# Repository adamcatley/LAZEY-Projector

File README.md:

LAZEY-Projector
===============

Collection of LAZEY Projector related files, split into firmware, software and hardware.

See http://lazeyprojector.blogspot.co.uk for more information.

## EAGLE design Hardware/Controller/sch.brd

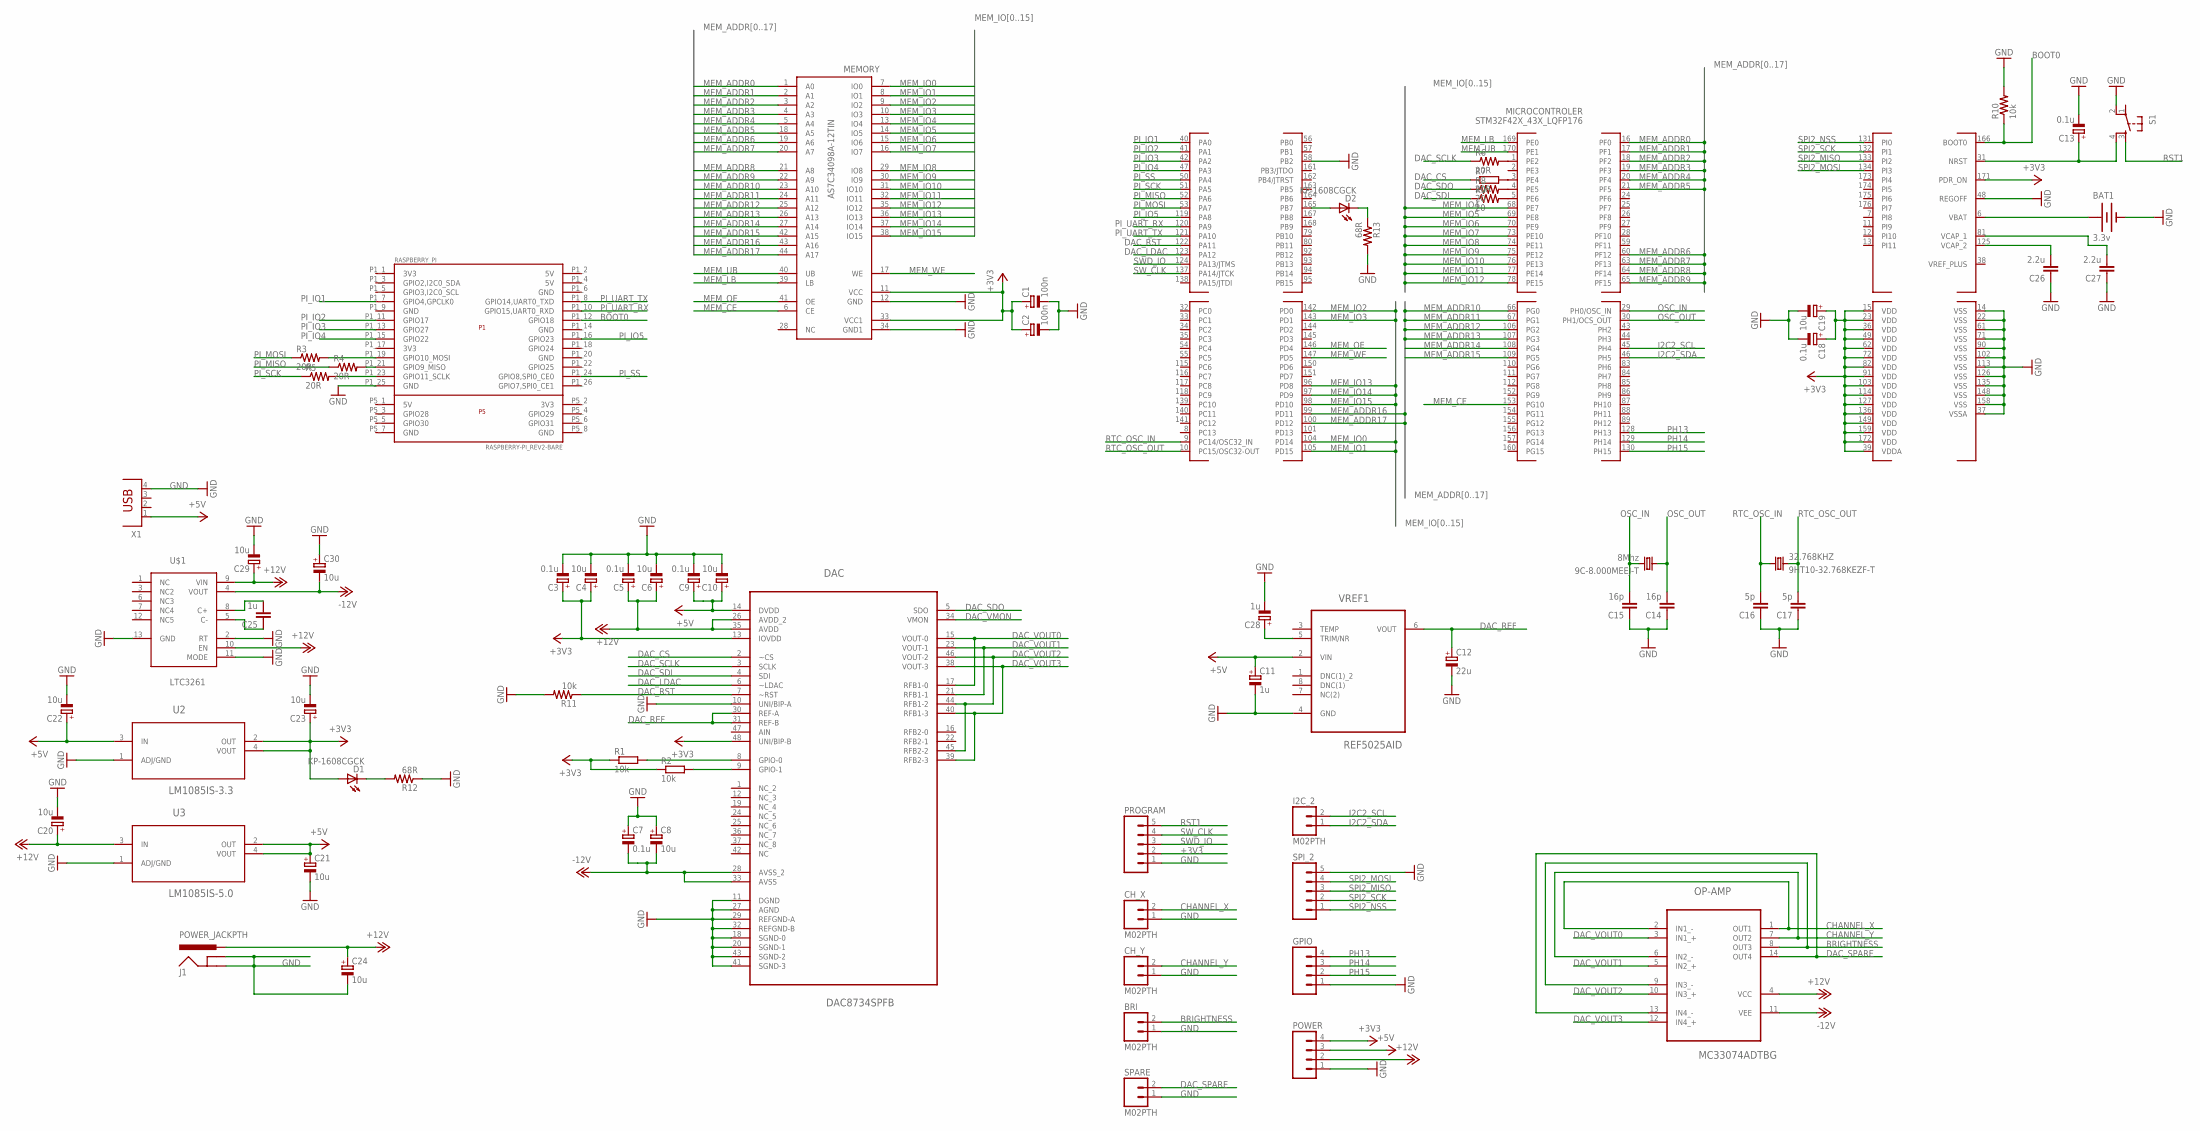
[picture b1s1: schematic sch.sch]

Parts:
9C-8.000MEEJ-T: 8Mhz; CSM-7X-DU
32.768KHZ: 9HT10-32.768KEZF-T
BAT1: 3.3v; BATTCON_12MM
BRI: M02PTH; 1X02
C1, C2: 100n; SMC_A
C3, C5, C7, C9, C13, C18: 0.1u; SMC_A
C4, C6, C8, C10, C19, C20, C21, C22, C23, C24, C29, C30: 10u; SMC_A
C11, C28: 1u; SMC_A
C12: 22u; SMC_A
C14, C15: 16p; C0603
C16, C17: 5p; C0603
C25: 1u; C0603
C26, C27: 2.2u; C0603
CH_X: M02PTH; 1X02
CH_Y: M02PTH; 1X02
D1, D2: KP-1608CGCK; LED-0603
DAC: DAC8734SPFB; QFP50P900X900X120-48N
GPIO: M04PTH; 1X04
I2C_2: M02PTH; 1X02
J1: POWER_JACKPTH; POWER_JACK_PTH
MEMORY: AS7C34098A-12TIN; TSOPII-44
MICROCONTROLER: STM32F42X_43X_LQFP176; LQFP176_PACKAGE
OP-AMP: MC33074ADTBG; SOP65P640X120-14N
POWER: M04PTH; 1X04
PROGRAM: M05PTH; 1X05
R1, R2: 10k; R0805
R3, R4, R5, R6: 20R; 0603-RES
R7: 20R; R0603
R8, R9: 20; 0603-RES
R10, R11: 10k; 0603-RES
R12, R13: 68R; 0603-RES
RASPBERRY_PI: RASPBERRY-PI_REV2-BARE
S1: TAC_SWITCHSMD; TACTILE_SWITCH_SMD
SPARE: M02PTH; 1X02
SPI_2: M05PTH; 1X05
U2: LM1085IS-3.3; TO254P1435X457-3N
U3: LM1085IS-5.0; TO254P1435X457-3N
U$1: LTC3261; MSOP12
VREF1: REF5025AID; SOIC127P600X175-8N
X1: PN87520

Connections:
+3V3: C1.+, C2.+, C3.+, C4.+, C18.+, C19.+, C23.+, D1.A, DAC.13 (IOVDD), DAC.48 (UNI/BIP-B), MEMORY.11 (VCC), MEMORY.33 (VCC1), MICROCONTROLER.15 (VDD), MICROCONTROLER.23 (VDD), MICROCONTROLER.36 (VDD), MICROCONTROLER.39 (VDDA), MICROCONTROLER.49 (VDD), MICROCONTROLER.62 (VDD), MICROCONTROLER.72 (VDD), MICROCONTROLER.82 (VDD), MICROCONTROLER.91 (VDD), MICROCONTROLER.103 (VDD), MICROCONTROLER.114 (VDD), MICROCONTROLER.127 (VDD), MICROCONTROLER.136 (VDD), MICROCONTROLER.149 (VDD), MICROCONTROLER.159 (VDD), MICROCONTROLER.171 (PDR_ON), MICROCONTROLER.172 (VDD), POWER.4, PROGRAM.2, R1.1, R2.1, U2.2 (OUT), U2.4 (VOUT)
+5V: C9.+, C10.+, C11.+, C21.+, C22.+, DAC.14 (DVDD), POWER.3, U2.3 (IN), U3.2 (OUT), U3.4 (VOUT), VREF1.2 (VIN), X1.1
+12V: C5.+, C6.+, C20.+, C24.+, C29.+, DAC.26 (AVDD_2), DAC.35 (AVDD), J1.PWR, OP-AMP.4 (VCC), POWER.2, U3.3 (IN), U$1.9 (VIN), U$1.10 (EN)
-12V: C7.-, C8.-, C30.-, DAC.28 (AVSS_2), DAC.33 (AVSS), OP-AMP.11 (VEE), U$1.4 (VOUT)
BOOT0: MICROCONTROLER.166 (BOOT0), R10.1, RASPBERRY_PI.P1_12 (GPIO18)
BRIGHTNESS: BRI.2, OP-AMP.8 (OUT3), OP-AMP.9 (IN3_-)
CHANNEL_X: CH_X.2, OP-AMP.1 (OUT1), OP-AMP.2 (IN1_-)
CHANNEL_Y: CH_Y.2, OP-AMP.6 (IN2_-), OP-AMP.7 (OUT2)
DAC_CS: DAC.2 (~CS), R7.1
DAC_LDAC: DAC.6 (~LDAC), MICROCONTROLER.123 (PA12)
DAC_REF: C12.+, DAC.30 (REF-A), DAC.31 (REF-B), VREF1.6 (VOUT)
DAC_RST: DAC.7 (~RST), MICROCONTROLER.122 (PA11), R11.1
DAC_SCLK: DAC.3 (SCLK), R6.1
DAC_SDI: DAC.4 (SDI), R9.1
DAC_SDO: DAC.5 (SDO), R8.1
DAC_SPARE: OP-AMP.13 (IN4_-), OP-AMP.14 (OUT4), SPARE.2
DAC_VMON: DAC.34 (VMON)
DAC_VOUT0: DAC.15 (VOUT-0), DAC.17 (RFB1-0), OP-AMP.3 (IN1_+)
DAC_VOUT1: DAC.21 (RFB1-1), DAC.23 (VOUT-1), OP-AMP.5 (IN2_+)
DAC_VOUT2: DAC.44 (RFB1-2), DAC.45 (RFB2-2), DAC.46 (VOUT-2), OP-AMP.10 (IN3_+)
DAC_VOUT3: DAC.38 (VOUT-3), DAC.39 (RFB2-3), DAC.40 (RFB1-3), OP-AMP.12 (IN4_+)
GND: BAT1.GND (-), BRI.1, C1.-, C2.-, C3.-, C4.-, C5.-, C6.-, C7.+, C8.+, C9.-, C10.-, C11.-, C12.-, C13.-, C14.1, C15.1, C16.1, C17.1, C18.-, C19.-, C20.-, C21.-, C22.-, C23.-, C24.-, C26.1, C27.1, C28.-, C29.-, C30.+, CH_X.1, CH_Y.1, DAC.10 (UNI/BIP-A), DAC.11 (DGND), DAC.18 (SGND-0), DAC.20 (SGND-1), DAC.27 (AGND), DAC.29 (REFGND-A), DAC.32 (REFGND-B), DAC.41 (SGND-3), DAC.43 (SGND-2), GPIO.1, J1.GND, J1.GNDBREAK, MEMORY.12 (GND), MEMORY.34 (GND1), MICROCONTROLER.14 (VSS), MICROCONTROLER.22 (VSS), MICROCONTROLER.37 (VSSA), MICROCONTROLER.48 (REGOFF), MICROCONTROLER.58 (PB2), MICROCONTROLER.61 (VSS), MICROCONTROLER.71 (VSS), MICROCONTROLER.90 (VSS), MICROCONTROLER.102 (VSS), MICROCONTROLER.113 (VSS), MICROCONTROLER.126 (VSS), MICROCONTROLER.135 (VSS), MICROCONTROLER.148 (VSS), MICROCONTROLER.158 (VSS), POWER.1, PROGRAM.1, R10.2, R11.2, R12.1, R13.2, RASPBERRY_PI.P1_25 (GND), S1.2, SPARE.1, SPI_2.5, U2.1 (ADJ/GND), U3.1 (ADJ/GND), U$1.2 (RT), U$1.11 (MODE), U$1.13 (GND), VREF1.4 (GND), X1.4
I2C2_SCL: I2C_2.2, MICROCONTROLER.45 (PH4)
I2C2_SDA: I2C_2.1, MICROCONTROLER.46 (PH5)
MEM_ADDR0: MEMORY.1 (A0), MICROCONTROLER.16 (PF0)
MEM_ADDR1: MEMORY.2 (A1), MICROCONTROLER.17 (PF1)
MEM_ADDR2: MEMORY.3 (A2), MICROCONTROLER.18 (PF2)
MEM_ADDR3: MEMORY.4 (A3), MICROCONTROLER.19 (PF3)
MEM_ADDR4: MEMORY.5 (A4), MICROCONTROLER.20 (PF4)
MEM_ADDR5: MEMORY.18 (A5), MICROCONTROLER.21 (PF5)
MEM_ADDR6: MEMORY.19 (A6), MICROCONTROLER.60 (PF12)
MEM_ADDR7: MEMORY.20 (A7), MICROCONTROLER.63 (PF13)
MEM_ADDR8: MEMORY.21 (A8), MICROCONTROLER.64 (PF14)
MEM_ADDR9: MEMORY.22 (A9), MICROCONTROLER.65 (PF15)
MEM_ADDR10: MEMORY.23 (A10), MICROCONTROLER.66 (PG0)
MEM_ADDR11: MEMORY.24 (A11), MICROCONTROLER.67 (PG1)
MEM_ADDR12: MEMORY.25 (A12), MICROCONTROLER.106 (PG2)
MEM_ADDR13: MEMORY.26 (A13), MICROCONTROLER.107 (PG3)
MEM_ADDR14: MEMORY.27 (A14), MICROCONTROLER.108 (PG4)
MEM_ADDR15: MEMORY.42 (A15), MICROCONTROLER.109 (PG5)
MEM_ADDR16: MEMORY.43 (A16), MICROCONTROLER.99 (PD11)
MEM_ADDR17: MEMORY.44 (A17), MICROCONTROLER.100 (PD12)
MEM_CE: MEMORY.6 (CE), MICROCONTROLER.153 (PG10)
MEM_IO0: MEMORY.7 (IO0), MICROCONTROLER.104 (PD14)
MEM_IO1: MEMORY.8 (IO1), MICROCONTROLER.105 (PD15)
MEM_IO2: MEMORY.9 (IO2), MICROCONTROLER.142 (PD0)
MEM_IO3: MEMORY.10 (IO3), MICROCONTROLER.143 (PD1)
MEM_IO4: MEMORY.13 (IO4), MICROCONTROLER.68 (PE7)
MEM_IO5: MEMORY.14 (IO5), MICROCONTROLER.69 (PE8)
MEM_IO6: MEMORY.15 (IO6), MICROCONTROLER.70 (PE9)
MEM_IO7: MEMORY.16 (IO7), MICROCONTROLER.73 (PE10)
MEM_IO8: MEMORY.29 (IO8), MICROCONTROLER.74 (PE11)
MEM_IO9: MEMORY.30 (IO9), MICROCONTROLER.75 (PE12)
MEM_IO10: MEMORY.31 (IO10), MICROCONTROLER.76 (PE13)
MEM_IO11: MEMORY.32 (IO11), MICROCONTROLER.77 (PE14)
MEM_IO12: MEMORY.35 (IO12), MICROCONTROLER.78 (PE15)
MEM_IO13: MEMORY.36 (IO13), MICROCONTROLER.96 (PD8)
MEM_IO14: MEMORY.37 (IO14), MICROCONTROLER.97 (PD9)
MEM_IO15: MEMORY.38 (IO15), MICROCONTROLER.98 (PD10)
MEM_LB: MEMORY.39 (LB), MICROCONTROLER.169 (PE0)
MEM_OE: MEMORY.41 (OE), MICROCONTROLER.146 (PD4)
MEM_UB: MEMORY.40 (UB), MICROCONTROLER.170 (PE1)
MEM_WE: MEMORY.17 (WE), MICROCONTROLER.147 (PD5)
unnamed: DAC.8 (GPIO-0), R1.2
unnamed: DAC.9 (GPIO-1), R2.2
unnamed: D1.C, R12.2
unnamed: D2.A, MICROCONTROLER.165 (PB7)
unnamed: R3.2, RASPBERRY_PI.P1_19 (GPIO10_MOSI)
unnamed: C25.2, U$1.8 (C+)
unnamed: R4.2, RASPBERRY_PI.P1_21 (GPIO9_MISO)
unnamed: R5.2, RASPBERRY_PI.P1_23 (GPIO11_SCLK)
unnamed: MICROCONTROLER.5 (PE6), R9.2
unnamed: MICROCONTROLER.4 (PE5), R8.2
unnamed: MICROCONTROLER.3 (PE4), R7.2
unnamed: MICROCONTROLER.1 (PE2), R6.2
unnamed: C25.1, U$1.5 (C-)
unnamed: D2.C, R13.1
unnamed: C26.2, MICROCONTROLER.125 (VCAP_2)
unnamed: C27.2, MICROCONTROLER.81 (VCAP_1)
unnamed: C28.+, VREF1.5 (TRIM/NR)
OSC_IN: 9C-8.000MEEJ-T.2, C15.2, MICROCONTROLER.29 (PH0/OSC_IN)
OSC_OUT: 9C-8.000MEEJ-T.1, C14.2, MICROCONTROLER.30 (PH1/OCS_OUT)
PH13: GPIO.4, MICROCONTROLER.128 (PH13)
PH14: GPIO.3, MICROCONTROLER.129 (PH14)
PH15: GPIO.2, MICROCONTROLER.130 (PH15)
PI_IO1: MICROCONTROLER.40 (PA0), RASPBERRY_PI.P1_7 (GPIO4,GPCLK0)
PI_IO2: MICROCONTROLER.41 (PA1), RASPBERRY_PI.P1_11 (GPIO17)
PI_IO3: MICROCONTROLER.42 (PA2), RASPBERRY_PI.P1_13 (GPIO27)
PI_IO4: MICROCONTROLER.47 (PA3), RASPBERRY_PI.P1_15 (GPIO22)
PI_IO5: MICROCONTROLER.119 (PA8), RASPBERRY_PI.P1_16 (GPIO23)
PI_MISO: MICROCONTROLER.52 (PA6), R4.1
PI_MOSI: MICROCONTROLER.53 (PA7), R3.1
PI_SCK: MICROCONTROLER.51 (PA5), R5.1
PI_SS: MICROCONTROLER.50 (PA4), RASPBERRY_PI.P1_24 (GPIO8,SPI0_CE0)
PI_UART_RX: MICROCONTROLER.120 (PA9), RASPBERRY_PI.P1_10 (GPIO15,UART0_RXD)
PI_UART_TX: MICROCONTROLER.121 (PA10), RASPBERRY_PI.P1_8 (GPIO14,UART0_TXD)
RST0: C13.+, MICROCONTROLER.31 (NRST), S1.4
RST1: PROGRAM.5, S1.3
RTC_OSC_IN: 32.768KHZ.P$1 (1), C16.2, MICROCONTROLER.9 (PC14/OSC32_IN)
RTC_OSC_OUT: 32.768KHZ.P$2 (2), C17.2, MICROCONTROLER.10 (PC15/OSC32-OUT)
SPI2_MISO: MICROCONTROLER.133 (PI2), SPI_2.3
SPI2_MOSI: MICROCONTROLER.134 (PI3), SPI_2.4
SPI2_NSS: MICROCONTROLER.131 (PI0), SPI_2.1
SPI2_SCK: MICROCONTROLER.132 (PI1), SPI_2.2
SWD_IO: MICROCONTROLER.124 (PA13/JTMS), PROGRAM.3
SW_CLK: MICROCONTROLER.137 (PA14/JTCK), PROGRAM.4
VBAT: BAT1.PWR@1 (+), MICROCONTROLER.6 (VBAT)

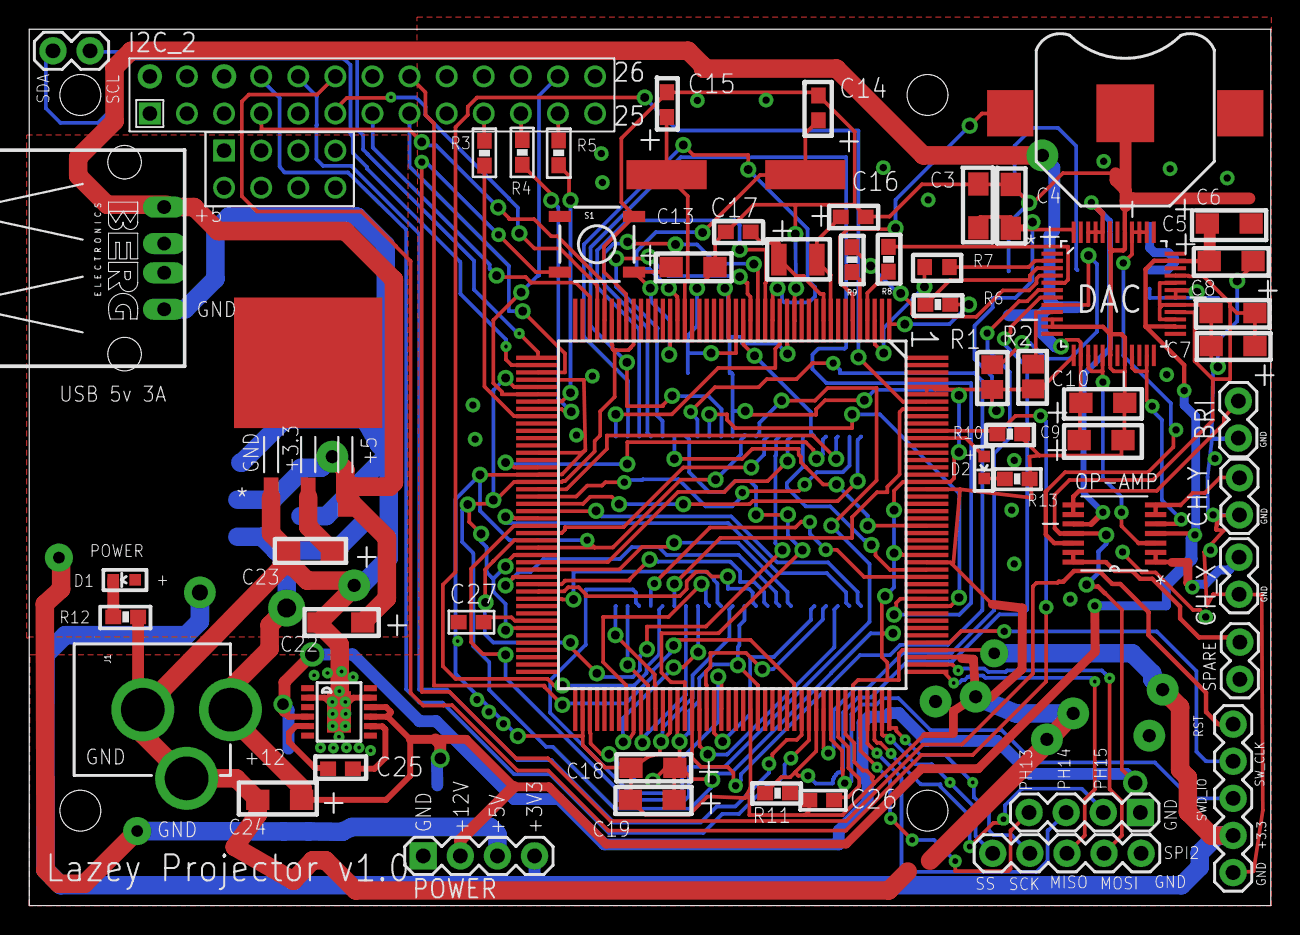
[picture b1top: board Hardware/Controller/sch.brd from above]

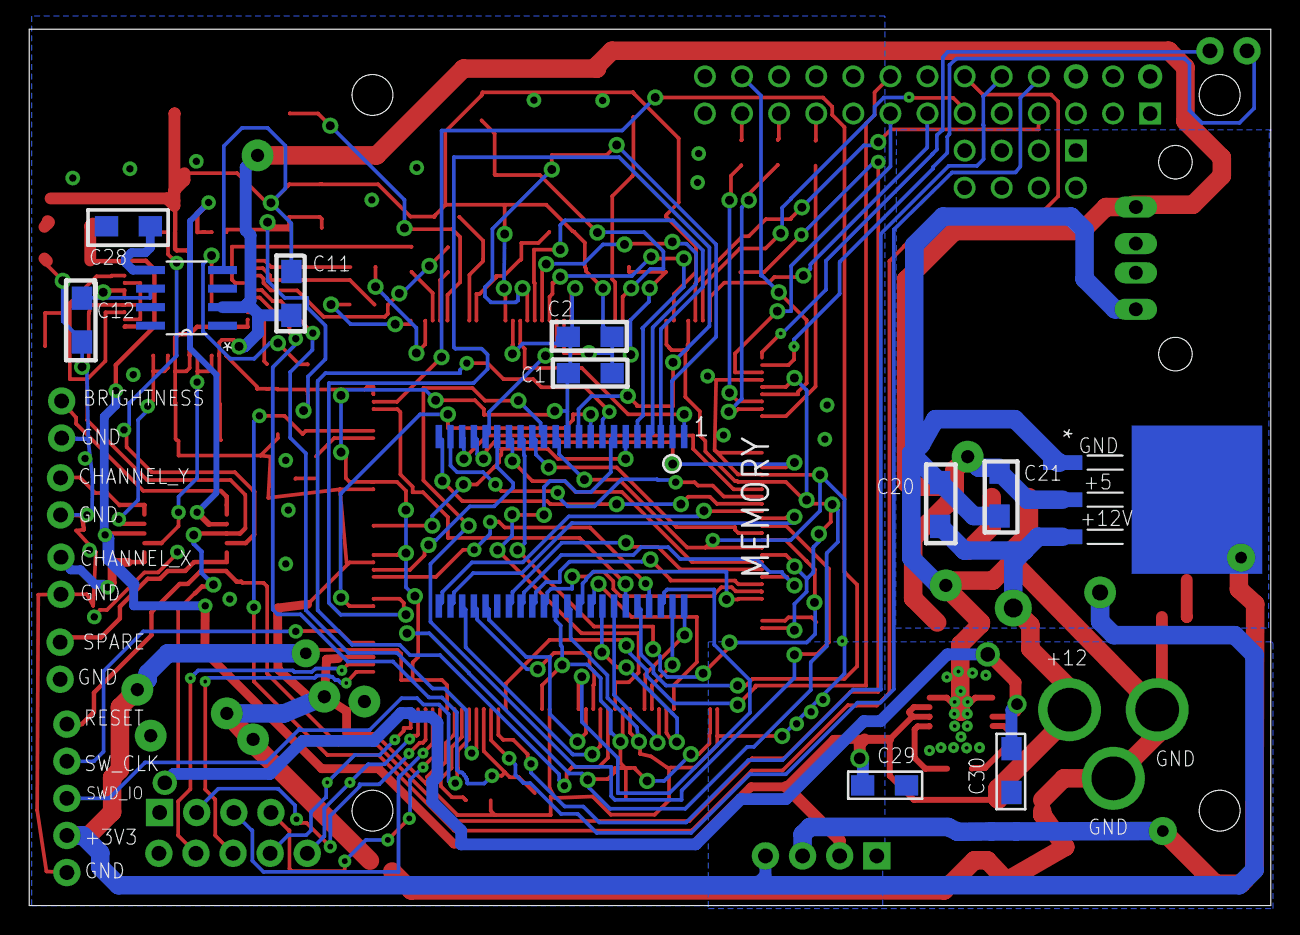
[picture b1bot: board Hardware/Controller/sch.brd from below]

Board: 2 copper layers, 85.0 x 60.0 mm, 69 parts (12 on the bottom side), 106 nets.

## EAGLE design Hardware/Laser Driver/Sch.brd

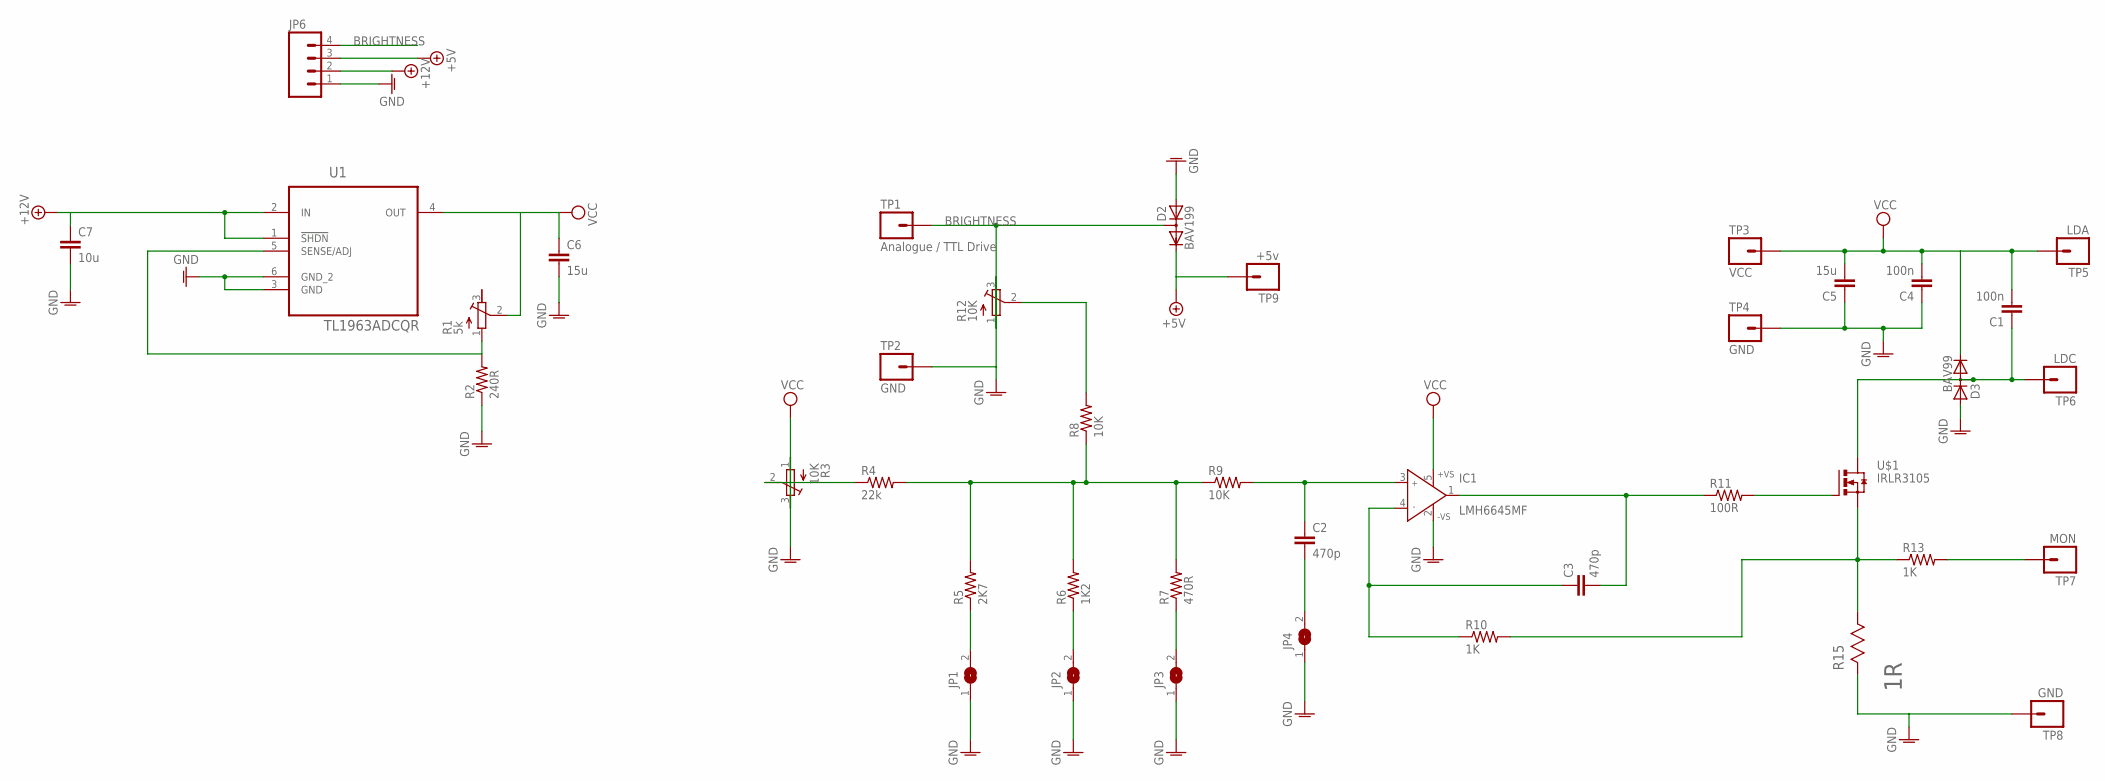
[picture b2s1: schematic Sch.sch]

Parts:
C1, C4: 100n; 1206
C2, C3: 470p; 1206
C5, C6: 15u; 1206
C7: 10u; 1206
D2: BAV199; SOT23
D3: BAV99; SOT23
IC1: LMH6645MF; SOT23-5
JP1, JP2, JP3, JP4: SJ
JP6: M04PTH; 1X04
R1: 5k; RTRIM64W
R2: 240R; 0603-RES
R3, R12: 10K; RTRIM5X
R4: 22k; 0603-RES
R5: 2K7; 0603-RES
R6: 1K2; 0603-RES
R7: 470R; 0603-RES
R8, R9: 10K; 0603-RES
R10, R13: 1K; 0603-RES
R11: 100R; R0603
R15: 1R; RESC5025X71N
TP1: Analogue / TTL Drive; 1X01
TP2, TP4, TP8: GND; 1X01
TP3: VCC; 1X01
TP5: LDA; 1X01_LONGPAD
TP6: LDC; 1X01_LONGPAD
TP7: MON; 1X01
TP9: +5v; 1X01
U1: TL1963ADCQR; SOT127P700X180-6N
U$1: IRLR3105; TO252AA-LARGE

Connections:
+5V: D2.2 (C), JP6.3, TP9.1
+12V: C7.1, JP6.2, U1.1 (!SHDN), U1.2 (IN)
BRIGHTNESS: D2.3 (AC), JP6.4, R12.1 (E), TP1.1
GNDA: C4.1, C5.1, C6.2, C7.2, D2.1 (A), D3.1 (A), IC1.2 (-VS), JP1.1, JP2.1, JP3.1, JP4.1, JP6.1, R2.1, R3.1 (E), R12.3 (A), R15.2 (R2), TP2.1, TP4.1, TP8.1, U1.3 (GND), U1.6 (GND_2)
unnamed: R8.2, R12.2 (S)
unnamed: R3.2 (S), R4.1
unnamed: R4.2, R5.2, R6.2, R7.2, R8.1, R9.1
unnamed: JP1.2, R5.1
unnamed: JP2.2, R6.1
unnamed: JP3.2, R7.1
unnamed: C2.2, JP4.2
unnamed: C2.1, IC1.3 (IN+), R9.2
unnamed: C3.1, IC1.4 (IN-), R10.1
unnamed: C3.2, IC1.1 (OUT), R11.1
unnamed: R11.2, U$1.P$1 (G)
unnamed: C1.1, D3.3 (AC), TP6.1, U$1.P$3 (D)
unnamed: R10.2, R13.1, R15.1 (R1), U$1.P$2 (S)
unnamed: R1.1 (E), R2.2, U1.5 (SENSE/ADJ)
unnamed: R13.2, TP7.1
VCC: C1.2, C4.2, C5.2, C6.1, D3.2 (C), IC1.5 (+VS), R1.2 (S), R3.3 (A), TP3.1, TP5.1, U1.4 (OUT)

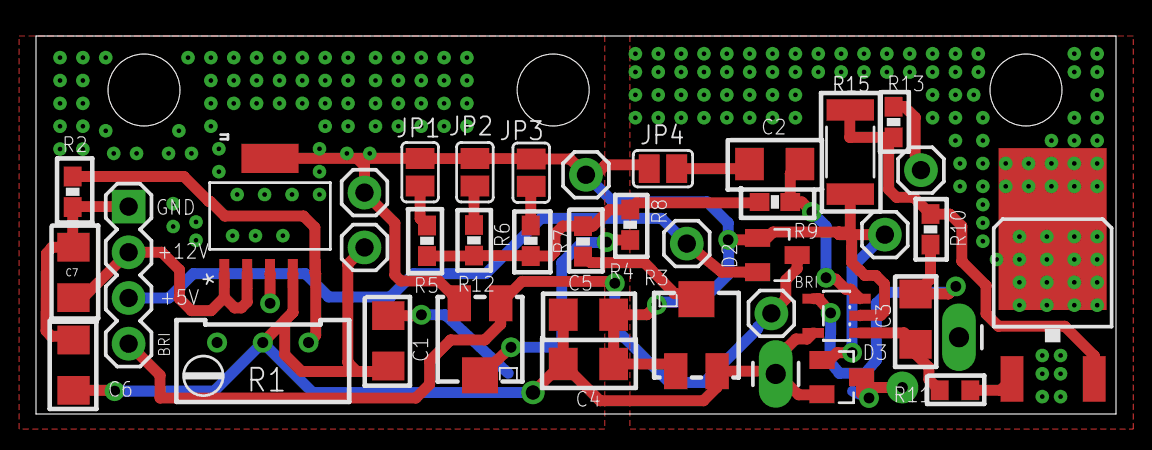
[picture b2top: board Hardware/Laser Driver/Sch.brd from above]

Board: 2 copper layers, 60.0 x 21.0 mm, 40 parts (0 on the bottom side), 20 nets.

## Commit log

2014-06-20 Proposed Structure
2014-06-20 Proposed Structure
    Folder structure for various project files
2014-09-18 Added hardware and software files
2014-09-18 Firmware added
2014-09-18 Firmware added
    Included compiled binary

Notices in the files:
parts and their libraries:
SparkFun-Electromechanical: Licensing: CC v3.0 Share-Alike You are welcome to use this library for commercial purposes.
